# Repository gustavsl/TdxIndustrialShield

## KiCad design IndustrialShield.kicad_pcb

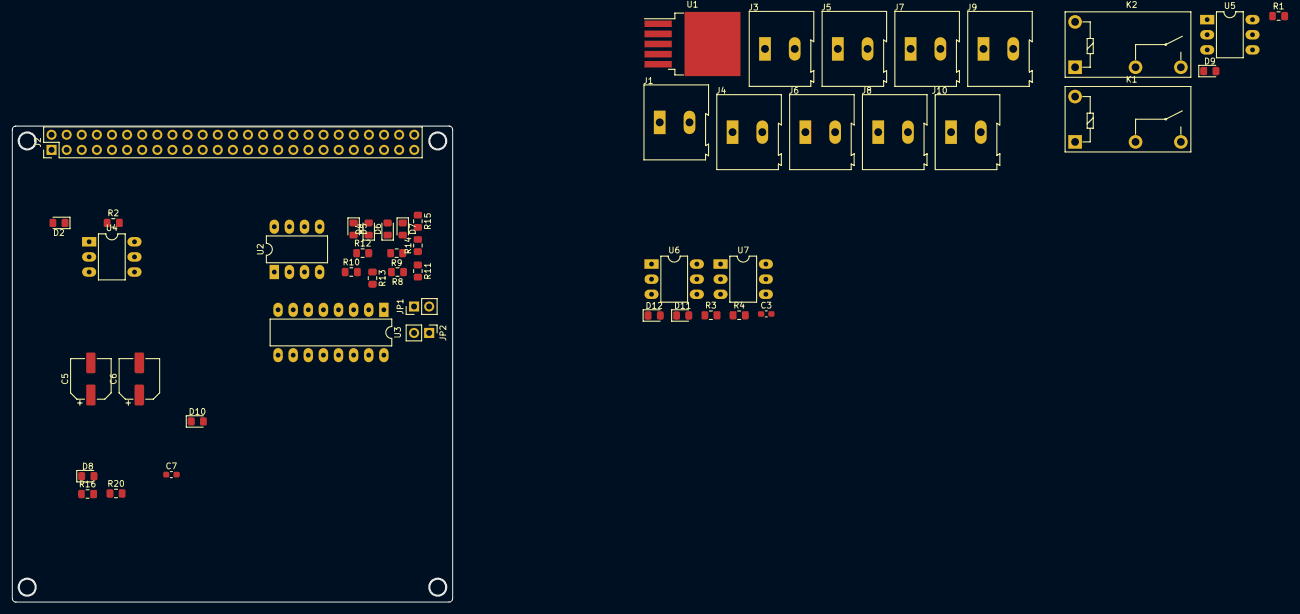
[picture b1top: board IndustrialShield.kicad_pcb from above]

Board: 2 copper layers, 74.0 x 80.0 mm, 49 parts (0 on the bottom side), 40 nets, no tracks yet.

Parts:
C3, C7: C_Small; C_0603_1608Metric_Pad1.05x0.95mm_HandSolder
C5, C6: 10u; CP_Elec_6.3x3
D2, D4, D5, D6, D7, D8, D9, D11: D_Small; D_0805_2012Metric_Pad1.15x1.40mm_HandSolder
D10, D12: LED_Small; LED_0805_2012Metric_Pad1.15x1.40mm_HandSolder
J1, J3, J4, J5, J6, J7, J8, J9, J10: Screw_Terminal_01x02; TerminalBlock_Altech_AK300-2_P5.00mm
J2: Viola Connector; PinHeader_2x25_P2.54mm_Vertical
JP1, JP2: Jumper_NC_Small; PinHeader_1x02_P2.54mm_Vertical
K1, K2: G5Q-1A; Relay_SPST_Omron-G5Q-1A
R1, R2, R4, R20: 330R; R_0805_2012Metric_Pad1.15x1.40mm_HandSolder
R3, R16: 4K7; R_0805_2012Metric_Pad1.15x1.40mm_HandSolder
R8, R9: 500R; R_0805_2012Metric_Pad1.15x1.40mm_HandSolder
R10, R11, R12, R13, R14, R15: 10K; R_0805_2012Metric_Pad1.15x1.40mm_HandSolder
U1: LM2596S-5.0; TO-263-5_TabPin3
U2: MAX485E; DIP-8_W7.62mm_LongPads
U3: MAX232; DIP-16_W7.62mm_LongPads
U4, U5, U6, U7: 4N25; DIP-6_W7.62mm_LongPads

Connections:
+3V3: D4.1, D6.1, J2.4, U2.8, U3.2, U3.16, U6.5, U7.5
+5V: J2.1, U1.4
+24V: D2.1, D9.1, K1.1, K2.1
/MAX232/RS232_RX: J3.2, U3.12
/MAX232/RS232_TX: J3.1, U3.14
/analog/0-10_4-20_1_P: J9.1, JP1.1, R10.2
/analog/0-10_4-20_2_P: J10.1, JP2.1, R11.2
/input/In1_N: C7.2, D8.2, J7.2, U6.2
/input/In1_P: J7.1, R16.2
/input/In2_N: C3.2, D11.2, J8.2, U7.2
/input/In2_P: J8.1, R3.2
AIN0: D4.2, D5.1, J2.47, R12.2, R13.1
AIN1: D6.2, D7.1, J2.48, R14.2, R15.1
GND: D5.2, D7.2, D10.1, D12.1, J2.7, J2.19, J2.24, J2.33, J2.40, J2.45, J9.2, J10.2, R1.2, R2.2, R8.1, R9.1, R13.2, R15.2, U1.3, U1.5, U2.5, U3.6, U3.15
GND_24V: J1.1, U4.4, U5.4
unnamed: C3.1, D11.1, R3.1, U7.1
unnamed: C5.1, U3.1
unnamed: C5.2, U3.3
unnamed: C6.1, U3.4
unnamed: C6.2, U3.5
unnamed: C7.1, D8.1, R16.1, U6.1
unnamed: D2.2, K1.5, U4.5
unnamed: D9.2, K2.5, U5.5
unnamed: D10.2, R20.1
unnamed: D12.2, R4.1
unnamed: JP1.2, R8.2
unnamed: JP2.2, R9.2
unnamed: R1.1, U5.2
unnamed: R2.1, U4.2
unnamed: R10.1, R12.1
unnamed: R11.1, R14.1
SODIMM_98: J2.9, R20.2, U6.4
SODIMM_103: J2.11, R4.2, U7.4
SODIMM_133: J2.10, U5.1
SODIMM_135: J2.8, U4.1
UARTB_RTS: J2.38, U2.2, U2.3
UARTB_RX: J2.37, U2.4
UARTB_TX: J2.36, U2.1
UARTC_RX: J2.35, U3.13
UARTC_TX: J2.34, U3.11

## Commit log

2020-01-02 fixes input and output circuits
2020-01-06 setting some component values
2020-01-06 selecting components, adds CAN
2020-01-08 added footprints
